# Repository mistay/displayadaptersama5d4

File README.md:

# displayadapter 3.5 to sama5d44 
device for attaching 4.3in displays to sama5

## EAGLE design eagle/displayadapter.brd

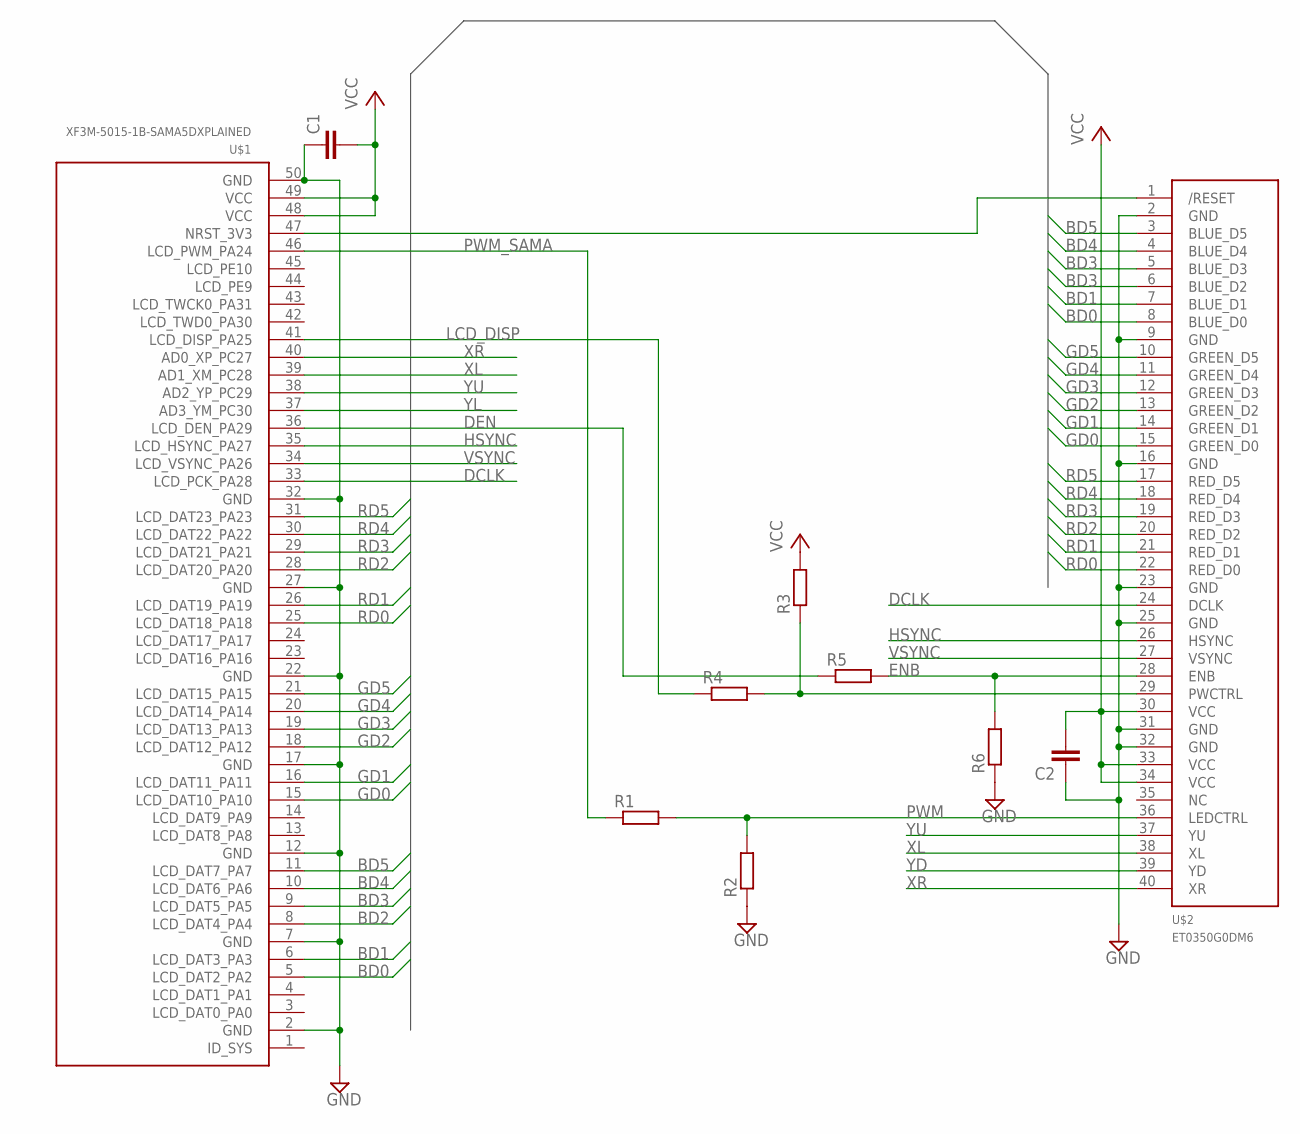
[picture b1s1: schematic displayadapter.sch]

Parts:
C1, C2: C-EUC0805; C0805
R1, R2, R3, R4, R5, R6: R-EU_M0805; M0805
U$1: XF3M-5015-1B-SAMA5DXPLAINED; XF3M-5015-1B
U$2: ET0350G0DM6; XF3M-4015-1B

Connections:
BD0: U$1.5 (LCD_DAT2_PA2), U$2.8 (BLUE_D0)
BD1: U$1.6 (LCD_DAT3_PA3), U$2.7 (BLUE_D1)
BD2: U$1.8 (LCD_DAT4_PA4), U$2.6 (BLUE_D2)
BD3: U$1.9 (LCD_DAT5_PA5), U$2.5 (BLUE_D3)
BD4: U$1.10 (LCD_DAT6_PA6), U$2.4 (BLUE_D4)
BD5: U$1.11 (LCD_DAT7_PA7), U$2.3 (BLUE_D5)
DCLK: U$1.33 (LCD_PCK_PA28), U$2.24 (DCLK)
DEN: R5.1, U$1.36 (LCD_DEN_PA29)
ENB: R5.2, R6.2, U$2.28 (ENB)
GD0: U$1.15 (LCD_DAT10_PA10), U$2.15 (GREEN_D0)
GD1: U$1.16 (LCD_DAT11_PA11), U$2.14 (GREEN_D1)
GD2: U$1.18 (LCD_DAT12_PA12), U$2.13 (GREEN_D2)
GD3: U$1.19 (LCD_DAT13_PA13), U$2.12 (GREEN_D3)
GD4: U$1.20 (LCD_DAT14_PA14), U$2.11 (GREEN_D4)
GD5: U$1.21 (LCD_DAT15_PA15), U$2.10 (GREEN_D5)
GND: C1.1, C2.1, R2.1, R6.1, U$1.2 (GND), U$1.7 (GND), U$1.12 (GND), U$1.17 (GND), U$1.22 (GND), U$1.27 (GND), U$1.32 (GND), U$1.50 (GND), U$2.2 (GND), U$2.9 (GND), U$2.16 (GND), U$2.23 (GND), U$2.25 (GND), U$2.31 (GND), U$2.32 (GND)
HSYNC: U$1.35 (LCD_HSYNC_PA27), U$2.26 (HSYNC)
LCD_DISP: R4.1, U$1.41 (LCD_DISP_PA25)
unnamed: R3.1, R4.2, U$2.29 (PWCTRL)
unnamed: U$1.47 (NRST_3V3), U$2.1 (/RESET)
PWM: R1.2, R2.2, U$2.36 (LEDCTRL)
PWM_SAMA: R1.1, U$1.46 (LCD_PWM_PA24)
RD0: U$1.25 (LCD_DAT18_PA18), U$2.22 (RED_D0)
RD1: U$1.26 (LCD_DAT19_PA19), U$2.21 (RED_D1)
RD2: U$1.28 (LCD_DAT20_PA20), U$2.20 (RED_D2)
RD3: U$1.29 (LCD_DAT21_PA21), U$2.19 (RED_D3)
RD4: U$1.30 (LCD_DAT22_PA22), U$2.18 (RED_D4)
RD5: U$1.31 (LCD_DAT23_PA23), U$2.17 (RED_D5)
VCC: C1.2, C2.2, R3.2, U$1.48 (VCC), U$1.49 (VCC), U$2.30 (VCC), U$2.33 (VCC), U$2.34 (VCC)
VSYNC: U$1.34 (LCD_VSYNC_PA26), U$2.27 (VSYNC)
XL: U$1.39 (AD1_XM_PC28), U$2.38 (XL)
XR: U$1.40 (AD0_XP_PC27), U$2.40 (XR)
YD: U$2.39 (YD)
YL: U$1.37 (AD3_YM_PC30)
YU: U$1.38 (AD2_YP_PC29), U$2.37 (YU)

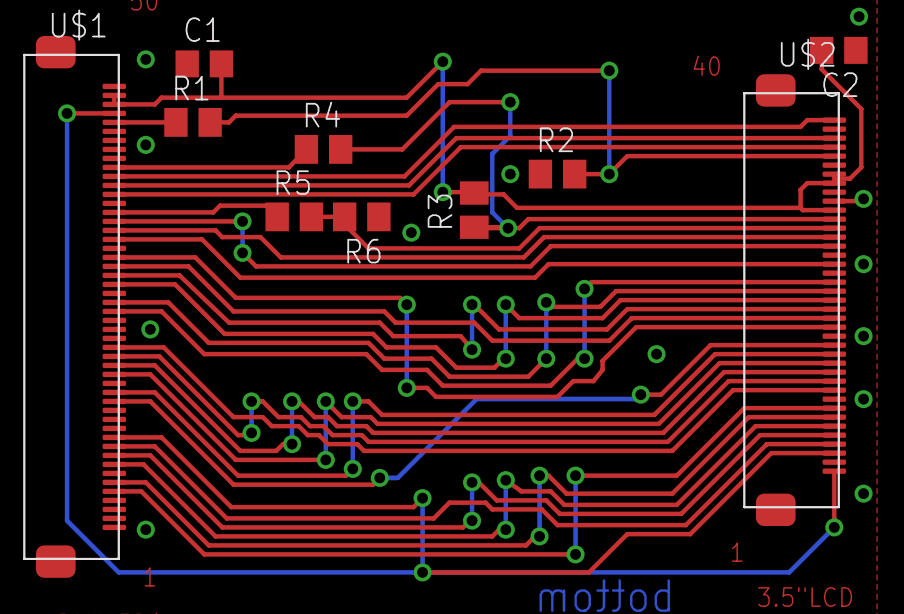
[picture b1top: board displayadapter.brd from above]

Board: 2 copper layers, 10 parts (0 on the bottom side), 33 nets.

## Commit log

2016-08-18 init commit
